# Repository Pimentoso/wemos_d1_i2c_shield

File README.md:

# wemos_d1_i2c_shield
Small Wemos D1 mini shield to easily solder multiple i2c devices

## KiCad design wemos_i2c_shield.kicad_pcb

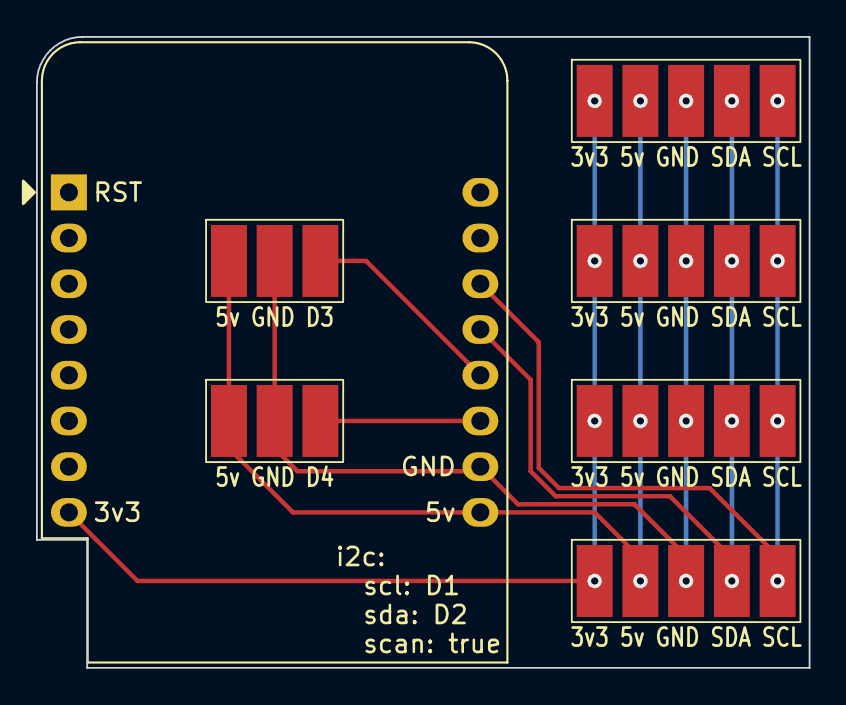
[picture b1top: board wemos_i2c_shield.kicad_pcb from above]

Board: 2 copper layers, 42.9 x 35.1 mm, 7 parts (0 on the bottom side), 7 nets.

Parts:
J1, J2, J3, J4: Conn_01x05_Pin; SolderPad_2.0x4.0mm_1x05
J5, J6: Conn_01x03_Pin; SolderPad_2.0x4.0mm_1x03
U1: WeMos_D1_mini; WEMOS_D1_mini_light

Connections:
3v3: J1.1, J2.1, J3.1, J4.1, U1.8 (3V3)
5v: J1.2, J2.2, J3.2, J4.2, J5.1, J6.1, U1.9 (5V)
D3: J5.3, U1.12 (D3)
D4: J6.3, U1.11 (D4)
GND: J1.3, J2.3, J3.3, J4.3, J5.2, J6.2, U1.10 (GND)
SCL: J1.5, J2.5, J3.5, J4.5, U1.14 (SCL/D1)
SDA: J1.4, J2.4, J3.4, J4.4, U1.13 (SDA/D2)

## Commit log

2024-04-05 cleanup
